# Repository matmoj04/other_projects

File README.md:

# Other/unfinished/abandoned projects
|    BRD   |   SCH    |
| :---: | :---: |
|       |       |
|       |       |

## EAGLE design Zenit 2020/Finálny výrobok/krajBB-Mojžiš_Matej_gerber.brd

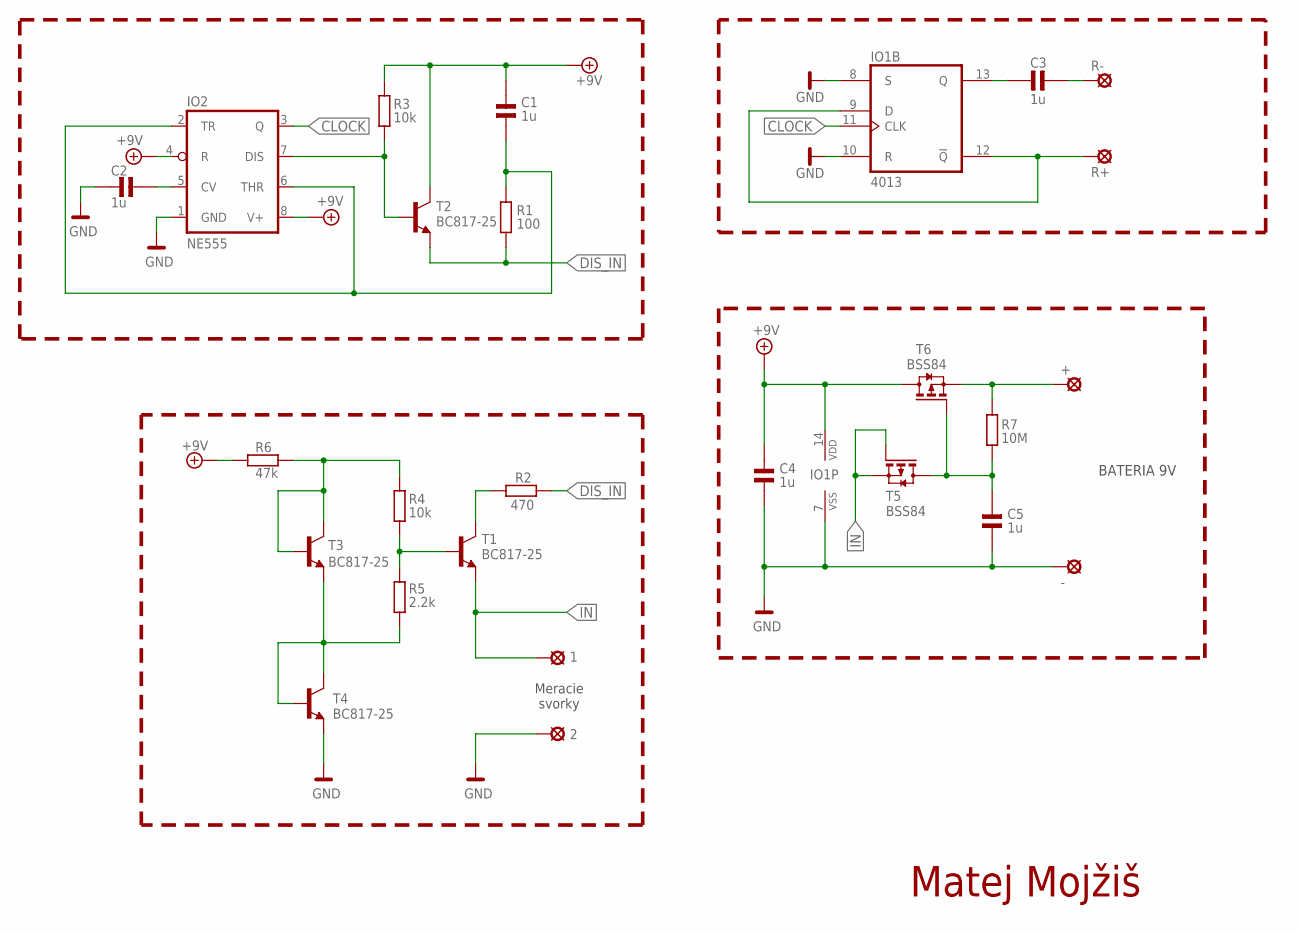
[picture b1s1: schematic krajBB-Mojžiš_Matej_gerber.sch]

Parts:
1, 2: SMD3X3
+: SMD3X3
-: SMD3X3
C1, C2, C3, C4, C5: 1u; 1206
IO1: 4013; SO14
IO2: NE555; SO08
R1: 100; 1206
R2: 470; 1206
R3, R4: 10k; 1206
R5: 2.2k; 1206
R6: 47k; 1206
R7: 10M; 1206
R+: SMD3X3
R-: SMD3X3
T1, T2, T3, T4: BC817-25; SOT23-BEC
T5, T6: BSS84; SOT23

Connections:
9V_1: R4.2, R6.1, T3.B, T3.C
9V_2: R5.1, T3.E, T4.B, T4.C
+9V: C1.2, C4.2, IO1.14 (VDD), IO2.4 (R), IO2.8 (V+), R3.2, R6.2, T2.C, T6.3 (D)
CLOCK: IO1.11 (CLK), IO2.3 (Q)
CV: C2.2, IO2.5 (CV)
DIS: IO2.7 (DIS), R3.1, T2.B
DIS_1: R2.1, T1.C
DIS_IN: R1.1, R2.2, T2.E
DIV: R4.1, R5.2, T1.B
GND: 2.P$1, -.P$1, C2.1, C4.1, C5.1, IO1.7 (VSS), IO1.8 (S), IO1.10 (R), IO2.1 (GND), T4.E
IN: 1.P$1, T1.E, T5.1 (G), T5.2 (S)
MOS: C5.2, R7.1, T5.3 (D), T6.1 (G)
OUT: C3.1, IO1.13 (Q)
REP: C3.2, R-.P$1
REP+: IO1.9 (D), IO1.12 (!Q), R+.P$1
THR: C1.1, IO2.2 (TR), IO2.6 (THR), R1.2
VIN: +.P$1, R7.2, T6.2 (S)

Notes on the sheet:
Meracie svorky
BATERIA 9V
Matej Mojžiš

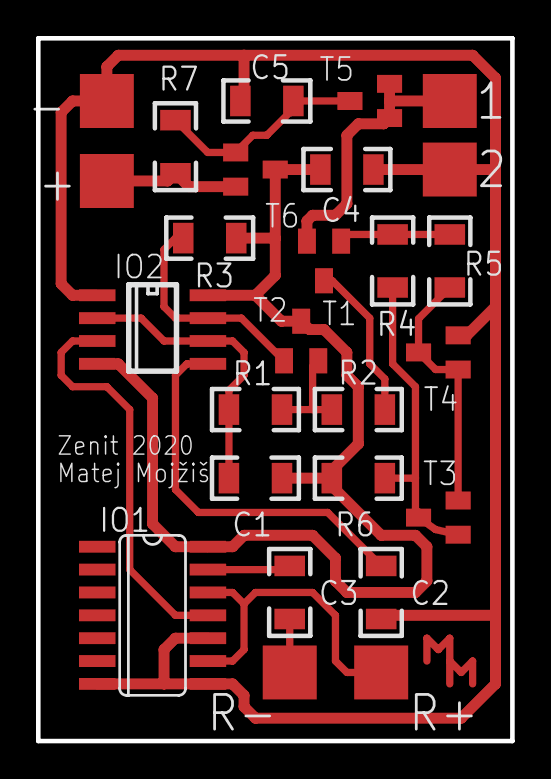
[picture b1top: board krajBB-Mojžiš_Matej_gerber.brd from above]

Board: 2 copper layers, 26.3 x 39.0 mm, 26 parts (0 on the bottom side), 17 nets.

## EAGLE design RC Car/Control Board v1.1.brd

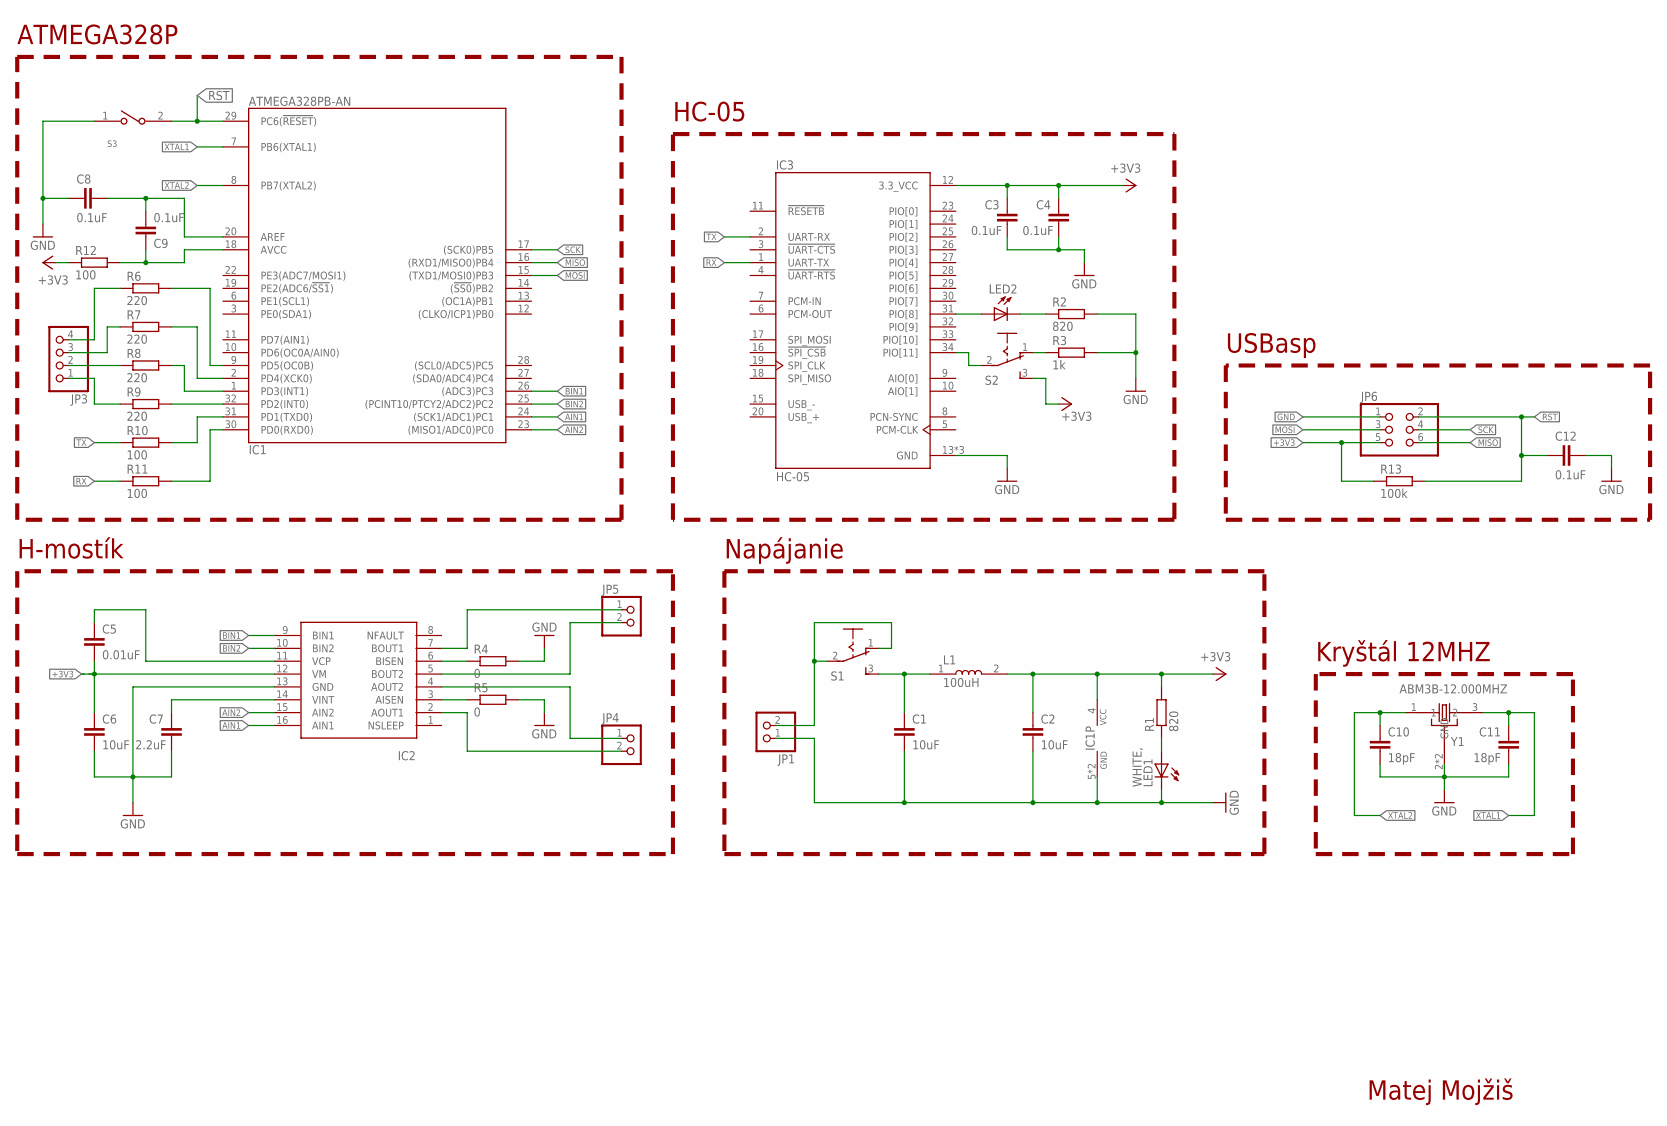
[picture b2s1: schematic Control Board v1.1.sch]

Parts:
C1, C2, C6: 10uF; C0805
C3, C4, C8, C9, C12: 0.1uF; C0805
C5: 0.01uF; C0805
C7: 2.2uF; C0805
C10, C11: 18pF; C0805
IC1: ATMEGA328PB-AN; QFP32_7X7_0.80
IC2: DVR8833SUPERFICIAL; PWP16
IC3: HC-05; XCVR_HC-05
JP1, JP4, JP5: 1X02/90
JP3: 1X04
JP6: 2X03
L1: 100uH; INDC2012X87N
LED1: WHITE,; CHIPLED_0805
LED2: RED; CHIPLED_0805
R1, R2: 820; R0805
R3: 1k; R0805
R4, R5: 0; R0805
R6, R7, R8, R9: 220; R0805
R10, R11, R12: 100; R0805
R13: 100k; R0805
S1, S2: 255SB
S3: SW_147873-2
Y1: ABM3B-12.000MHZ; OSCSC500X320X110-4N

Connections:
3V7: C1.1, L1.1, S1.3 (S)
+3V3: C2.1, C3.1, C4.1, C5.2, C6.1, IC1.4 (VCC), IC2.12 (VM), IC3.12 (3.3_VCC), JP6.5, L1.2, R1.2, R12.1, R13.1, S2.3 (S)
+3V7: JP1.2, S1.1 (O), S1.2
AIN1: IC1.24 ((SCK1/ADC1)PC1), IC2.16 (AIN1)
AIN2: IC1.23 ((MISO1/ADC0)PC0), IC2.15 (AIN2)
AISEN: IC2.3 (AISEN), R5.1
AOUT1: IC2.2 (AOUT1), JP4.2
AOUT2: IC2.4 (AOUT2), JP4.1
AREF: C8.1, C9.2, IC1.20 (AREF)
AVCC: C9.1, IC1.18 (AVCC), R12.2
BACK: JP3.2, R8.1
BIN1: IC1.26 ((ADC3)PC3), IC2.9 (BIN1)
BIN2: IC1.25 ((PCINT10/PTCY2/ADC2)PC2), IC2.10 (BIN2)
BISEN: IC2.6 (BISEN), R4.1
BOUT1: IC2.7 (BOUT1), JP5.1
BOUT2: IC2.5 (BOUT2), JP5.2
FRONT: JP3.1, R9.1
GND: C1.2, C2.2, C3.2, C4.2, C6.2, C7.2, C8.2, C10.2, C11.2, C12.1, IC1.5 (GND), IC1.21 (GND), IC2.13 (GND), IC3.13 (GND), IC3.21 (GND), IC3.22 (GND), JP1.1, JP6.1, LED1.C, R2.2, R3.2, R4.2, R5.2, S3.1, Y1.2 (GND), Y1.4 (GND)
IN: LED1.A, R1.1
INRX: IC1.30 (PD0(RXD0)), R11.2
LED: LED2.C, R2.1
LEFT: JP3.3, R7.1
MISO: IC1.16 ((RXD1/MISO0)PB4), JP6.6
MOSI: IC1.15 ((TXD1/MOSI0)PB3), JP6.3
OUTTX: IC1.31 (PD1(TXD0)), R10.2
PD2: IC1.32 (PD2(INT0)), R9.2
PD3: IC1.1 (PD3(INT1)), R8.2
PD4: IC1.2 (PD4(XCK0)), R7.2
PD5: IC1.9 (PD5(OC0B)), R6.2
PIO8: IC3.31 (PIO[8]), LED2.A
PIO11: IC3.34 (PIO[11]), S2.2
RIGHT: JP3.4, R6.1
RST: C12.2, IC1.29 (PC6(!RESET!)), JP6.2, R13.2, S3.2
RX: IC3.1 (UART-TX), R11.1
S: R3.1, S2.1 (O)
SCK: IC1.17 ((SCK0)PB5), JP6.4
TX: IC3.2 (UART-RX), R10.1
VCP: C5.1, IC2.11 (VCP)
VINT: C7.1, IC2.14 (VINT)
XTAL1: C11.1, IC1.7 (PB6(XTAL1)), Y1.3 (2)
XTAL2: C10.1, IC1.8 (PB7(XTAL2)), Y1.1

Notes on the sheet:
Napájanie
USBasp
H-mostík
Kryštál 12MHZ
ATMEGA328P
HC-05
Matej Mojžiš

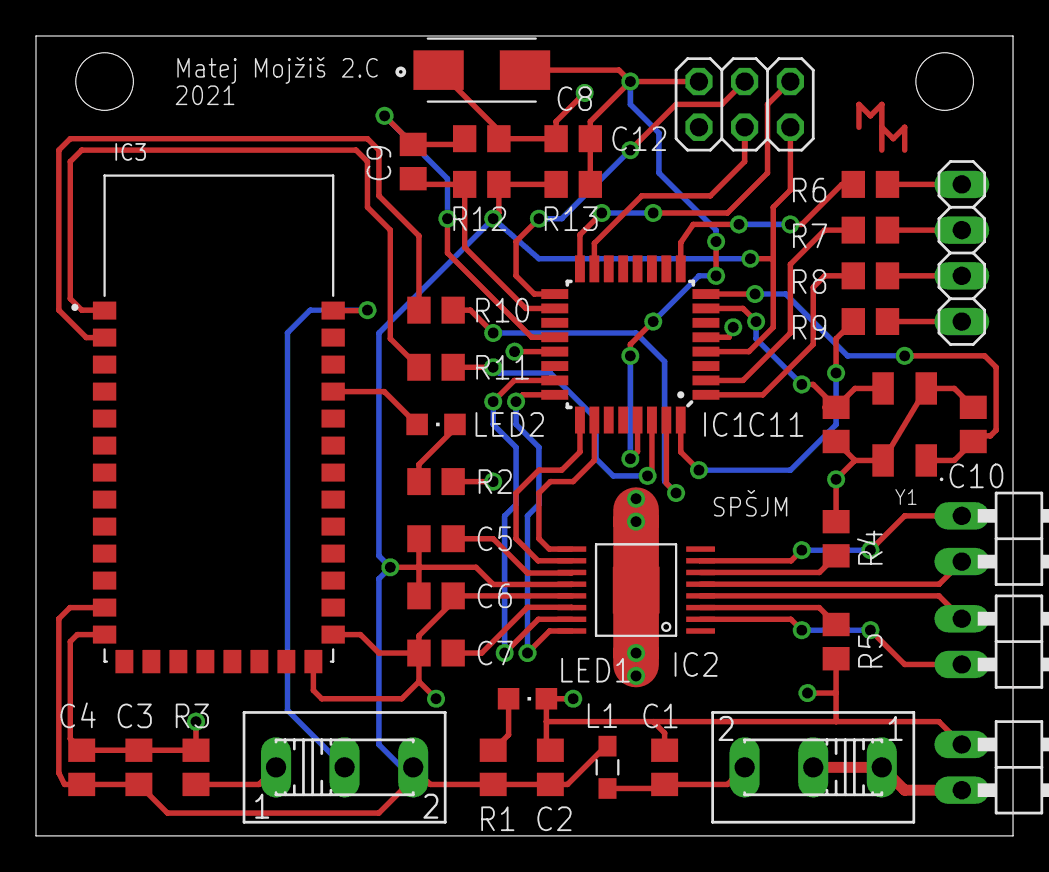
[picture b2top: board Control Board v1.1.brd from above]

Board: 2 copper layers, 54.3 x 44.4 mm, 40 parts (0 on the bottom side), 41 nets.

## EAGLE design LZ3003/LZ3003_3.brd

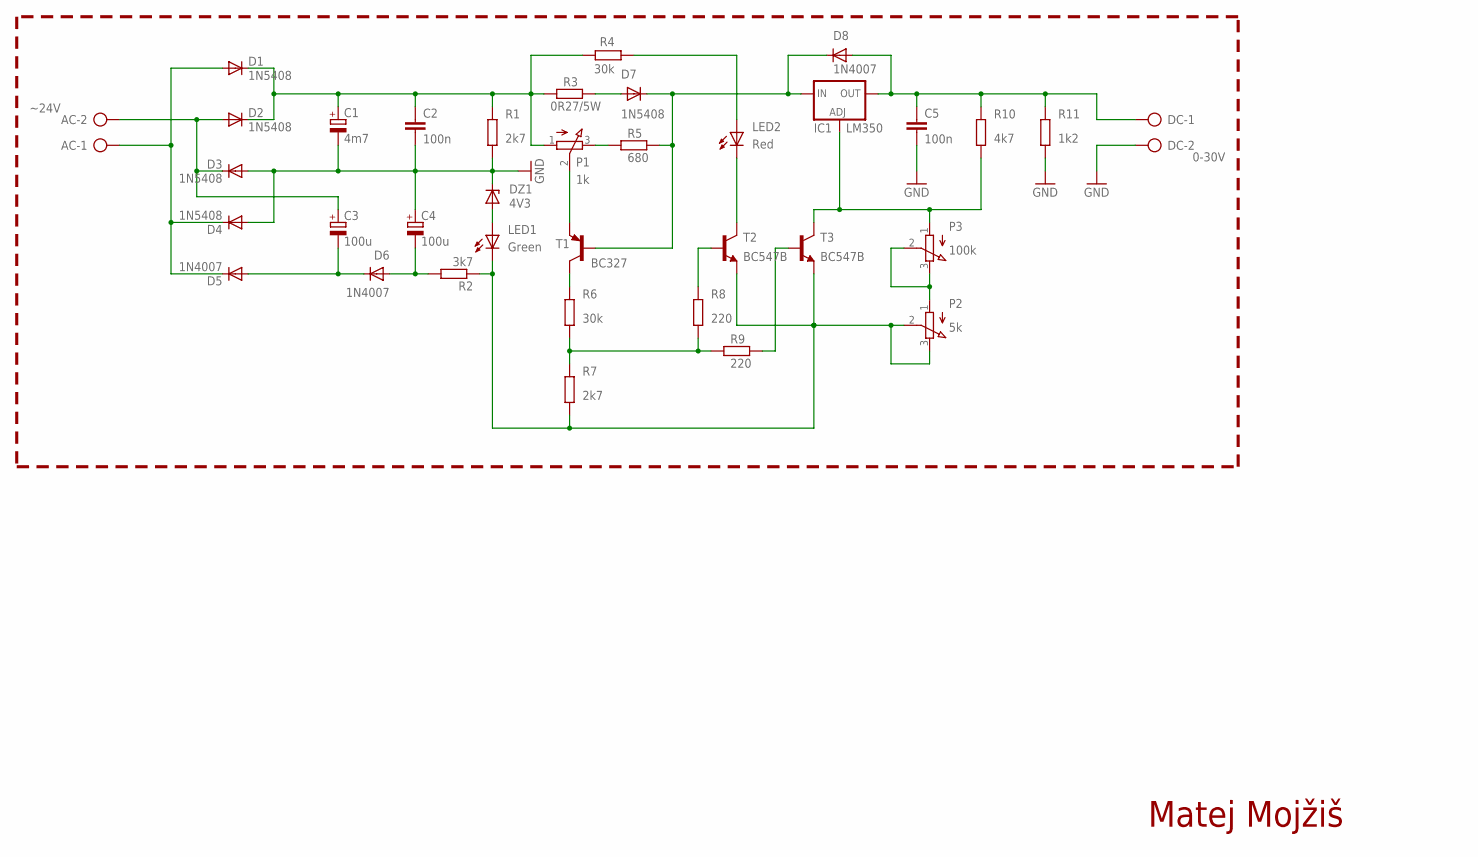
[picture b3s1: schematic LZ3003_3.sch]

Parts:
AC: ~24V; W237-102
C1: 4m7; E7,5-16
C2, C5: 100n; C050-025X075
C3, C4: 100u; E5-8,5
D1, D2, D3, D4, D7: 1N5408; DO201-15
D5, D6, D8: 1N4007; DO41-10
DC: 0-30V; W237-102
DZ1: 4V3; DO34Z7
IC1: LM350; 317TS
LED1: Green; LED5MM
LED2: Red; LED5MM
P1: 1k; 3RP/1610N
P2: 5k; 3RP/1610N
P3: 100k; 3RP/1610N
R1, R7: 2k7; 0207/7
R2: 3k7; 0207/7
R3: 0R27/5W; 0617/22
R4, R6: 30k; 0207/7
R5: 680; 0207/7
R8, R9: 220; 0207/7
R10: 4k7; 0207/7
R11: 1k2; 0207/7
T1: BC327; TO92-EBC
T2, T3: BC547B; TO92-CBE

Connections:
ADJ: IC1.1 (ADJ), P3.1 (A), R10.1, T3.C
ADJ1: P2.1 (A), P3.2 (S), P3.3 (E)
C: R6.2, T1.C
CC: LED2.K (C), T2.C
DC11: C3.-, D5.A, D6.C
DC+: C1.+, C2.1, D1.C, D2.C, P1.1 (A), R1.1, R3.1, R4.2
DC-: LED1.K (C), P2.2 (S), P2.3 (E), R2.1, R7.1, T2.E, T3.E
E: P1.2 (S), T1.E
GND: C1.-, C2.2, C4.+, C5.2, D3.A, D4.A, DC.2, DZ1.C, R1.2, R11.1
IN: D7.C, D8.C, IC1.3 (IN), R5.2, T1.B
L: AC.2, C3.+, D2.A, D3.C
LIM: D7.A, R3.2
LIMM: LED2.A, R4.1
LMMM: C4.-, D6.A, R2.2
N: AC.1, D1.A, D4.C, D5.C
OUT: C5.1, D8.A, DC.1, IC1.2 (OUT), R10.2, R11.2
SET: R9.2, T3.B
SET1: R6.1, R7.2, R8.1, R9.1
SETT: P1.3 (E), R5.1
SETTT: R8.2, T2.B
ZEN: DZ1.A, LED1.A

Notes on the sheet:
Matej Mojžiš

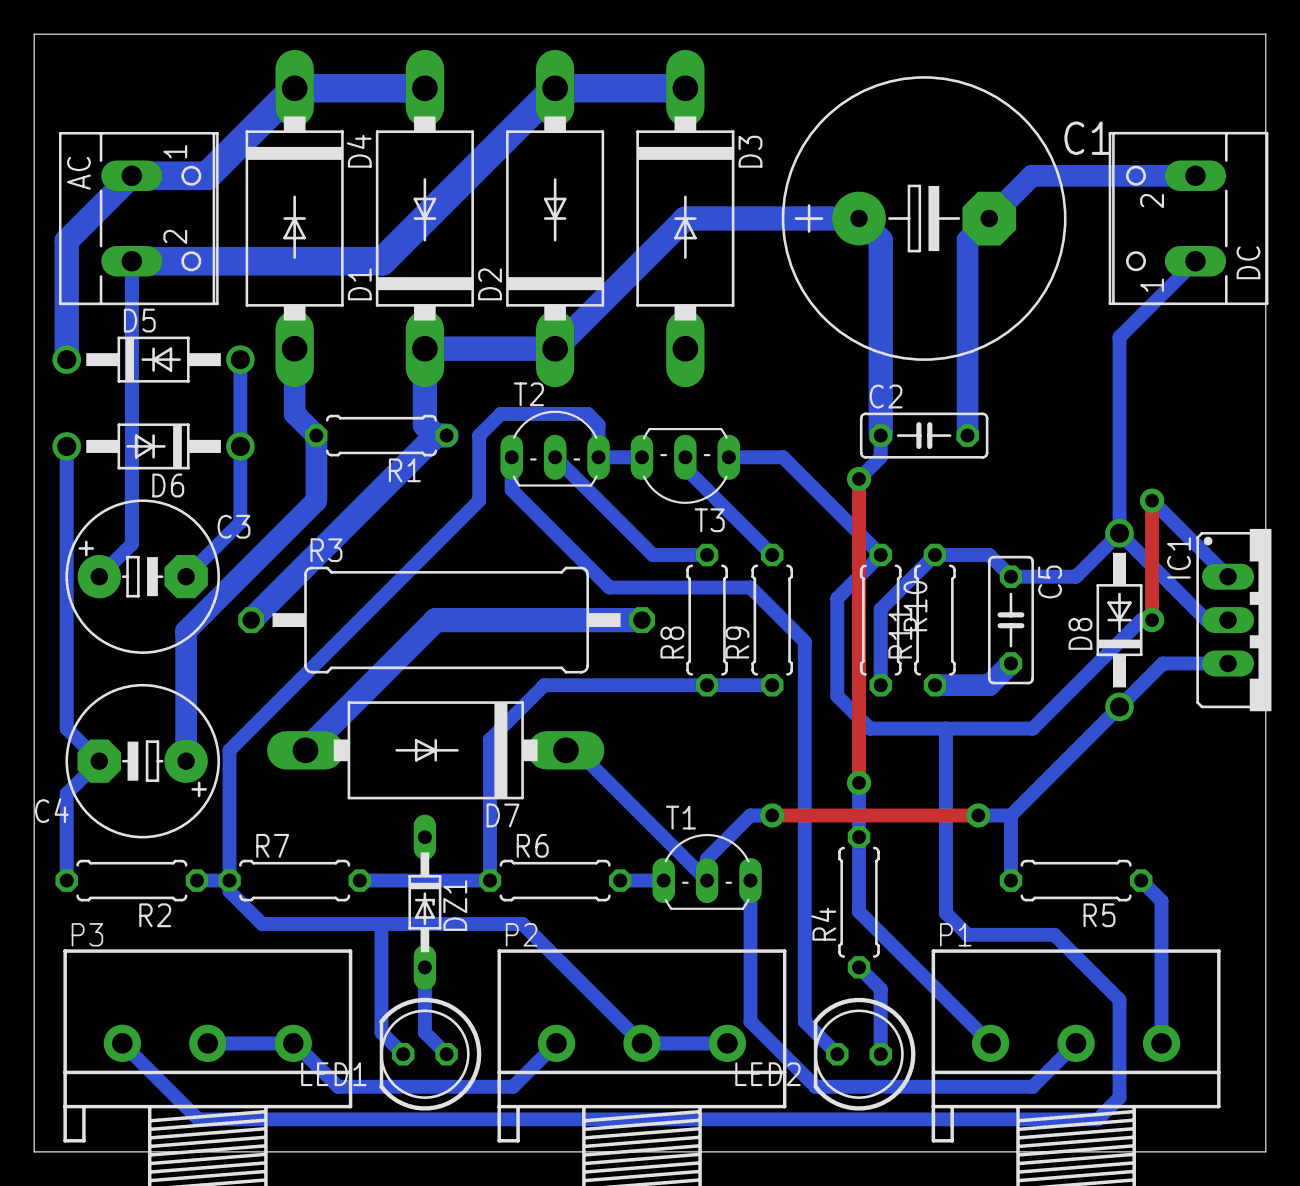
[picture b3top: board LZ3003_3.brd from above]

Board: 2 copper layers, 72.1 x 65.4 mm, 36 parts (0 on the bottom side), 21 nets.

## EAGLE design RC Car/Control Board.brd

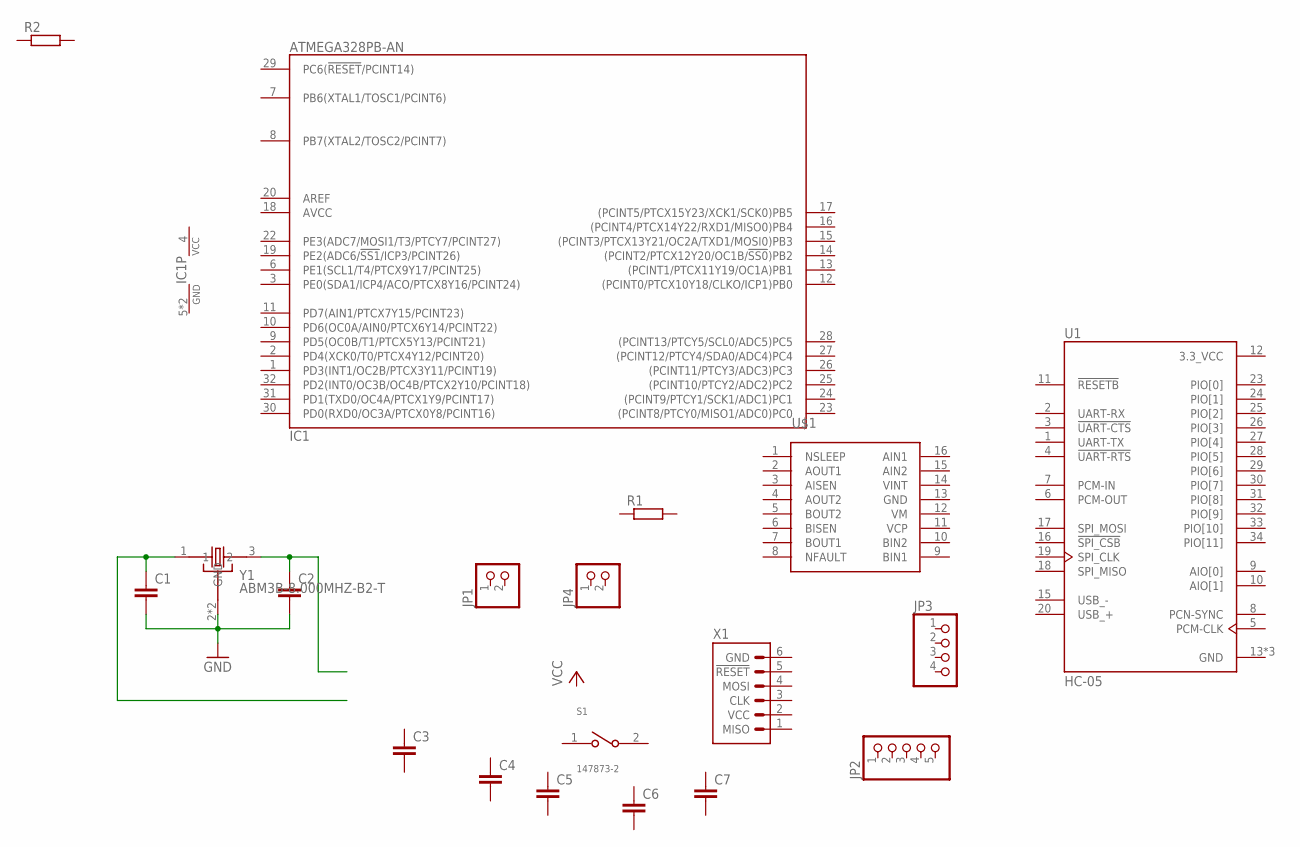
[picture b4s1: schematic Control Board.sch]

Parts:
C1, C2, C3, C4, C5, C6, C7: C-EUC0805; C0805
IC1: ATMEGA328PB-AN; QFP32_7X7_0.80
JP1, JP4: PINHD-1X2/90; 1X02/90
JP2: PINHD-1X5/90; 1X05/90
JP3: PINHD-1X4; 1X04
R1: R-EU_0207/7; 0207/7
R2: R-EU_VTA55; VTA55
S1: 147873-2; SW_147873-2
U1: HC-05; XCVR_HC-05
U$1: DVR8833SUPERFICIAL; PWP16
X1: MISO_MOSITHT_100MIL; PINHEADER_2R03_100MIL
Y1: ABM3B-8.000MHZ-B2-T; OSCSC500X320X110-4N

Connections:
3.3_VCC: U1.12 (3.3_VCC)
AVCC: IC1.18 (AVCC)
GND: C1.2, C2.2, IC1.5 (GND), IC1.21 (GND), U1.13 (GND), U1.21 (GND), U1.22 (GND), Y1.2 (GND), Y1.4 (GND)
unnamed: C1.1, Y1.1
unnamed: C2.1, Y1.3 (2)
VCC: IC1.4 (VCC)

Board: 2 copper layers, 19 parts (0 on the bottom side), 3 nets, no tracks yet.

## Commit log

2024-10-01 Other projects.
2024-10-01 New files
2024-10-02 Zenit competition.
